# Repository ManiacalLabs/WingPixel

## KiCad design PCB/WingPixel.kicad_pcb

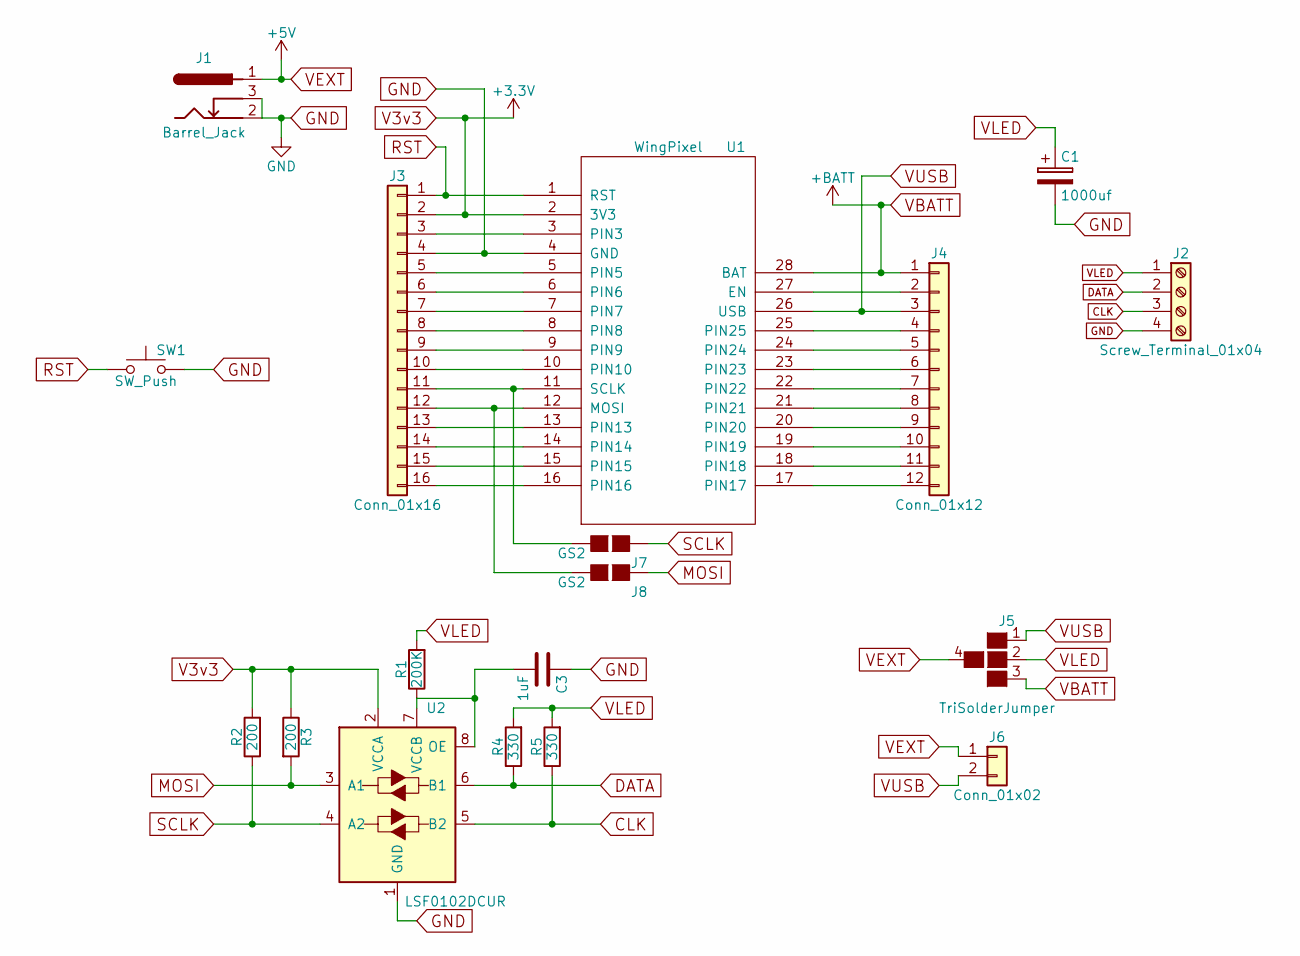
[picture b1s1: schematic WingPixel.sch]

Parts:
C1: 1000uf; CP_Elec_10x10
C3: 1uF; C_0603
J1: Barrel_Jack; ML_BARREL_JACK_ROUND_PADS_SHORT
J2: Screw_Terminal_01x04; mpt_0,5%2f4-2,54
J3: Conn_01x16; Pin_Header_Straight_1x16_Pitch2.54mm
J4: Conn_01x12; Pin_Header_Straight_1x12_Pitch2.54mm
J5: TriSolderJumper; TriSelectSolderJumper_HighCurrent
J6: Conn_01x02; Pin_Header_Straight_1x02_Pitch2.54mm
J7, J8: GS2; 2-PinCutTrace
R1: 200K; R_0603
R2, R3: 200; R_0603
R4, R5: 330; R_0603
SW1: SW_Push; SW_SPST_KMR2
U1: WingPixel; FeatherWing_NoOutline
U2: LSF0102DCUR; VSSOP-8_2.4x2.1mm_Pitch0.5mm

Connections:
CLK: J2.3, R5.1, U2.5 (B2)
DATA: J2.2, R4.1, U2.6 (B1)
GND: C1.2, C3.1, J1.2, J1.3, J2.4, J3.4, SW1.2, U1.4 (GND), U2.1 (GND)
MOSI: J8.1 (G1), R3.2, U2.3 (A1)
unnamed: C3.2, R1.1, U2.7 (VCCB), U2.8 (OE)
unnamed: J3.3, U1.3 (PIN3)
unnamed: J3.5, U1.5 (PIN5)
unnamed: J3.6, U1.6 (PIN6)
unnamed: J3.7, U1.7 (PIN7)
unnamed: J3.8, U1.8 (PIN8)
unnamed: J3.9, U1.9 (PIN9)
unnamed: J3.10, U1.10 (PIN10)
unnamed: J3.11, J7.2 (G2), U1.11 (SCLK)
unnamed: J3.12, J8.2 (G2), U1.12 (MOSI)
unnamed: J3.13, U1.13 (PIN13)
unnamed: J3.14, U1.14 (PIN14)
unnamed: J3.15, U1.15 (PIN15)
unnamed: J3.16, U1.16 (PIN16)
unnamed: J4.2, U1.27 (EN)
unnamed: J4.4, U1.25 (PIN25)
unnamed: J4.5, U1.24 (PIN24)
unnamed: J4.6, U1.23 (PIN23)
unnamed: J4.7, U1.22 (PIN22)
unnamed: J4.8, U1.21 (PIN21)
unnamed: J4.9, U1.20 (PIN20)
unnamed: J4.10, U1.19 (PIN19)
unnamed: J4.11, U1.18 (PIN18)
unnamed: J4.12, U1.17 (PIN17)
RST: J3.1, SW1.1, U1.1 (RST)
SCLK: J7.1 (G1), R2.1, U2.4 (A2)
V3v3: J3.2, R2.2, R3.1, U1.2 (3V3), U2.2 (VCCA)
VBATT: J4.1, J5.3, U1.28 (BAT)
VEXT: J1.1, J5.4, J6.1
VLED: C1.1, J2.1, J5.2 (1), R1.2, R4.2, R5.2
VUSB: J4.3, J5.1, J6.2, U1.26 (USB)

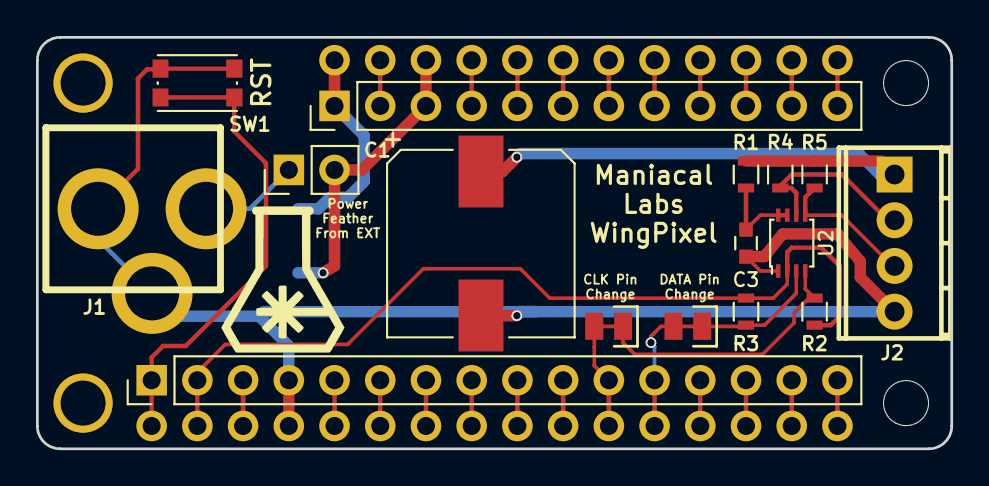
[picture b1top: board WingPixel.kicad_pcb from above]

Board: 2 copper layers, 50.8 x 22.9 mm, 18 parts (1 on the bottom side), 35 nets.

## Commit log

2018-03-09 Changing power distribution
2018-03-09 Adjusted Power Distribution, defined zones
2018-03-09 Saved Project, Sch, and PCB
2018-03-10 Connected VUSB, VBATT, Modified Zone for VEXT
2018-03-13 Cleaned up Silk Screen, Added Labels and Logos
2018-03-21 Converted to 2-Layer board(!)
2018-03-21 Fixed Fthr footprint drill/pad size, jmpr labels
2018-03-22 Final PCB cleanup, fixed LvlShft wiring.
2018-06-17 Adding 32u4 examples
2018-06-17 Adding 328p examples
2018-06-17 Adding ESP8266, starting on M0
2018-06-17 Adding ESP32
2018-06-17 Adding Teensy examples
2018-06-18 Added placeholders for cuttable traces
2018-06-24 Rotated Cap
2018-06-24 Added Cut Trace footprints, moved cap and logo.
2018-06-24 Adjusted via, generated gerber files for Seeed Quote
